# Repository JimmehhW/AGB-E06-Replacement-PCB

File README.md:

# [Read the License!](LICENSE.txt)
# AGB-E06-Replacement-PCB
Replacement PCB for damaged gameboy advance games using the AGB-E06 pcb
## Credits
Thanks to HDR for the symbols and footprints for the board outline, cart bus, mask rom, battery pads and a few ground pads.  
His repo can be found [here](https://github.com/HDR/NintendoPCBs).
### General Info
Please note this PCB can only be used as a replacement board for an original game.  
  
Order at 0.8mm and with ENIG, **NOT HASL**.  
### SRAM vs FRAM
***As a quick note, if your donor board has a working SRAM I would generally reccomend you simply use that and not go out of your way to get a new FRAM chip since a battery save will likely last more than long enough for most people.***  
  
  This board works with both the original save chip (SRAM) OR a replacement new part, a FM18W08 (FRAM) with the benefit of the FRAM being that a battery is not required to maintain the save. If FRAM is used, do not install a battery and instead populate R5 with a 10k ohm resistor (sized for 0603), this goes between pins 20 and 28 of the FM18W08 to act as a pullup resistor since the functionality of its chip enable pin is inverted compared to the original SRAM.  
  As a side note, the SRAM/FRAM footprint on the board is sized for the FM18W08 which is slightly smaller than the original SRAM, although I haven't had any trouble getting the original SRAM on. 
### BOM 
|Designator|Component|
|----------|---------|
|C1,C2,C3,C4,C6|0402 0.1uF|
|C5|0603 ?|
|R1|0402 1k|
|R2,R4|0402 100k|
|R3|0402 5k|
|R5|0603 10k (FRAM ONLY!)|
|BT1|CR1616 Tabbed|
|U1|harvested (MX23L6406-12C)|
|U2|harvested (BS62LV256SC-70) OR FM18W08|
|U3|harvested (BU9803F)|
|U4|harvested (PST3425)|

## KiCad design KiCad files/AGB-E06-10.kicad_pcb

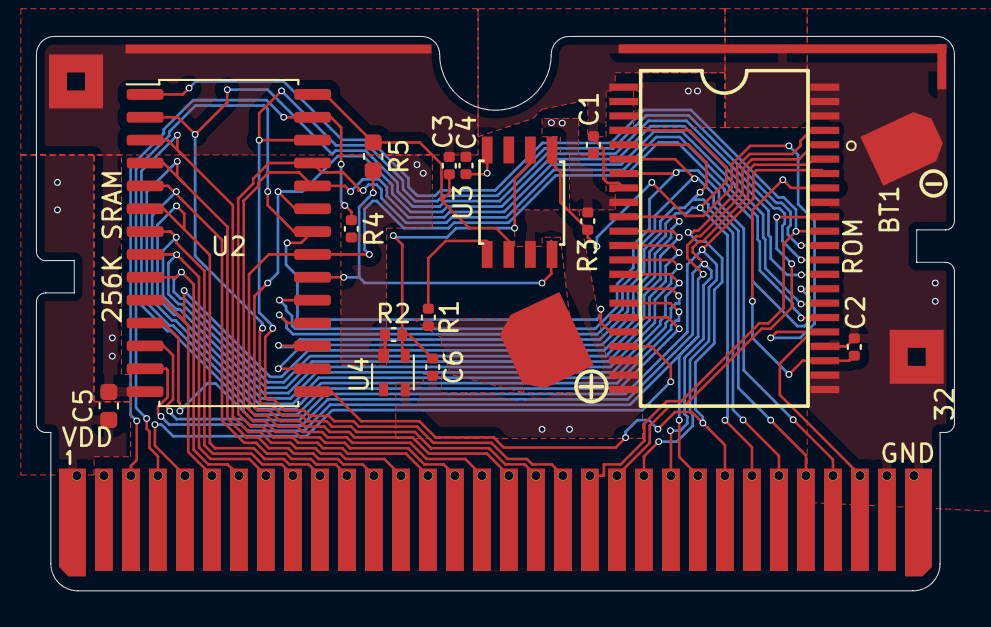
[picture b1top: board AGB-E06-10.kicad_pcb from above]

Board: 2 copper layers, 51.0 x 30.8 mm, 21 parts (0 on the bottom side), 35 nets.

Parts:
A2, A3: 3x3Pad; 3x3mm_Pad
A6: CartBrow_Left; AGB-Cartbrow_Left
A7: CartBrow_Right; AGB-Cartbrow_Right
BT1: CR1616; AGB-CR1616
C1: 127nF; C_0402_1005Metric
C2: 116nF; C_0402_1005Metric
C3: 130nF; C_0402_1005Metric
C4: 113nF; C_0402_1005Metric
C5: ??; C_0603_1608Metric
C6: 122nF; C_0402_1005Metric
R1: 1k; C_0402_1005Metric
R2, R4: 100k; C_0402_1005Metric
R3: 5k; C_0402_1005Metric
R5: 10k; C_0603_1608Metric
U0: CartBus; AGB_Cartridge
U1: MX23L12806-12C; AGB-TSOP-II-44_10.16x18.41mm_P0.8mm
U2: FM18W08-SG; SOIC-28W_7.5x17.9mm_P1.27mm
U3: TSSOP-8_3x3mm_P0.65mm
U4: PST4325

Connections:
+3V3: C1.1, C2.1, C4.1, C5.1, R2.1, R3.1, R4.1, U0.1 (VCC), U1.3 (VCC), U1.9 (VCC), U1.25 (VCC), U1.37 (VCC), U3.8 (Vcc), U4.2 (Vcc)
A0: U0.6 (A0), U1.10 (A0), U2.10 (A0)
A1: U0.7 (A1), U1.11 (A1), U2.9 (A1)
A2: U0.8 (A2), U1.12 (A2), U2.8 (A2)
A3: U0.9 (A3), U1.13 (A3), U2.7 (A3)
A4: U0.10 (A4), U1.14 (A4), U2.6 (A4)
A5: U0.11 (A5), U1.15 (A5), U2.5 (A5)
A6: U0.12 (A6), U1.16 (A6), U2.4 (A6)
A7: U0.13 (A7), U1.17 (A7), U2.3 (A7)
A8: U0.14 (A8), U1.28 (A8), U2.25 (A8)
A9: U0.15 (A9), U1.29 (A9), U2.24 (A9)
A10: U0.16 (A10), U1.30 (A10), U2.21 (A10)
A11: U0.17 (A11), U1.31 (A11), U2.23 (A11)
A12: U0.18 (A12), U1.32 (A12), U2.2 (A12)
A13: U0.19 (A13), U1.33 (A13), U2.26 (A13)
A14: U0.20 (A14), U1.34 (A14), U2.1 (A14)
A15: U0.21 (A15), U1.35 (A15)
CS: U0.5 (CS), U1.19 (CS)
CS2: R3.2, U0.30 (RST), U1.27 (CS2), U3.5 (CS2)
D0: U0.22 (D0), U1.38 (D0), U2.11 (DQ0)
D1: U0.23 (D1), U1.39 (D1), U2.12 (DQ1)
D2: U0.24 (D2), U1.40 (D2), U2.13 (DQ2)
D3: U0.25 (D3), U1.41 (D3), U2.15 (DQ3)
D4: U0.26 (D4), U1.4 (D4), U2.16 (DQ4)
D5: U0.27 (D5), U1.5 (D5), U2.17 (DQ5)
D6: U0.28 (D6), U1.6 (D6), U2.18 (DQ6)
D7: U0.29 (D7), U1.7 (D7), U2.19 (DQ7)
GND: A2.1, A3.1, A6.1, A7.1, BT1.2 (-), C1.2, C2.2, C3.2, C4.2, C5.2, C6.2, U0.31 (SND), U0.32 (GND), U1.1 (GND), U1.8 (GND), U1.20 (GND), U1.21 (GND), U1.22 (GND), U1.23 (GND), U1.24 (GND), U1.26 (GND), U1.36 (GND), U1.42 (GND), U1.43 (GND), U1.44 (GND), U2.14 (VSS), U3.3 (GND), U4.4 (Vss)
unnamed: BT1.1 (+), R1.2
unnamed: R1.1, U3.1 (Vss)
unnamed: C3.1, R5.1, U2.28 (VDD), U3.2 (Vout)
unnamed: R5.2, U2.20 (~CE), U3.4 (CE)
unnamed: C6.1, R2.2, U3.6 (Vss), U4.1 (Vout)
RD: U0.4 (RD), U1.18 (RD), U2.22 (~OE)
WR: R4.2, U0.3 (WR), U2.27 (~WE)
